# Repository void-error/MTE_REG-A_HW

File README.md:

# MTE_REG-A_HW
Voltage regulators for the analog section

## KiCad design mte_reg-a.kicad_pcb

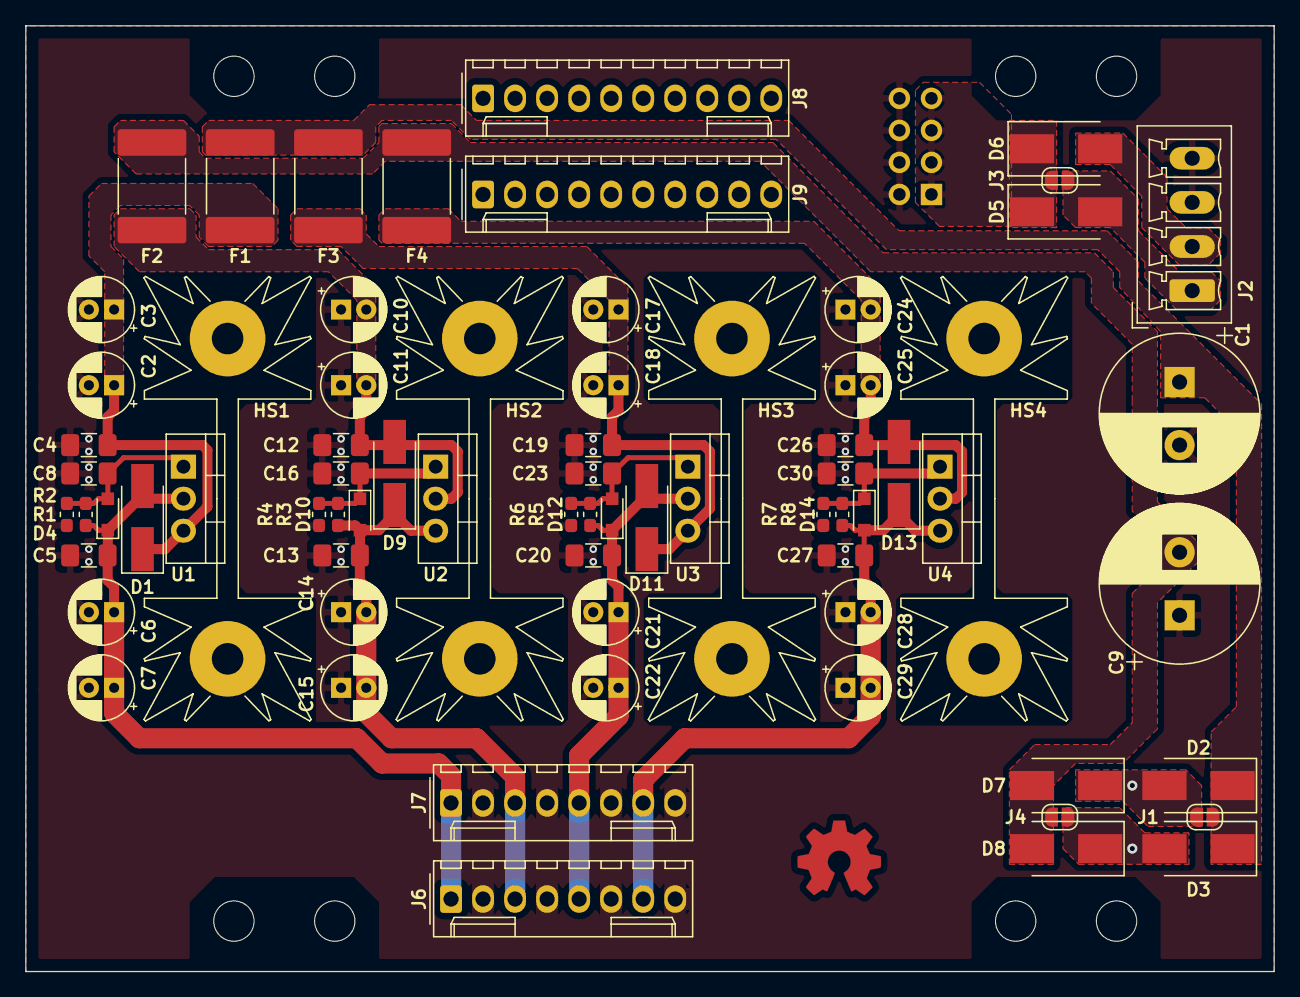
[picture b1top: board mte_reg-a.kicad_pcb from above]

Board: 2 copper layers, 99.0 x 75.0 mm, 82 parts (1 on the bottom side), 28 nets.

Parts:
C1, C9: 1000u; CP_Radial_D12.5mm_P5.00mm
C2, C3, C6, C7, C10, C11, C14, C15, C17, C18, C21, C22, C24, C25, C28, C29: 33u; CP_Radial_D5.0mm_P2.00mm
C4, C5, C12, C13, C19, C20, C26, C27: 330n; C_1206_3216Metric_Pad1.42x1.75mm_HandSolder
C8, C16, C23, C30: 2u2; C_1206_3216Metric_Pad1.42x1.75mm_HandSolder
D1, D9, D11, D13: S1A; D_SMA_Handsoldering
D2, D3, D5, D6, D7, D8: SK55; D_SMB_Handsoldering
D4, D10, D12, D14: BAS316; D_SOD-323_HandSoldering
F1, F2, F3, F4: SL075-33; Fuse_2920_7451Metric_Pad2.10x5.45mm_HandSolder
HS1, HS2, HS3, HS4: SK104; Heatsink_Fischer_SK104-STC-STIC_35x13mm_2xDrill2.5mm
J1, J3, J4: GS2; SolderJumper-2_P1.3mm_Open_RoundedPad1.0x1.5mm
J2: Conn_01x04; PhoenixContact_MCV_1,5_4-G-3.5_1x04_P3.50mm_Vertical
J5: Conn_02x04_Odd_Even; PinSocket_2x04_P2.54mm_Vertical
J6, J7: MOLEX_KK-254; Molex_KK-254_AE-6410-08A_1x08_P2.54mm_Vertical
J8, J9: Conn_01x10; Molex_KK-254_AE-6410-10A_1x10_P2.54mm_Vertical
LOGO1: OSHW; OSHW-Symbol_6.7x6mm_Copper
MK1, MK2, MK3, MK4, MK5, MK6, MK7, MK8: Mounting_Hole; MountingHole_3.2mm_M3
R1, R3, R5, R7: 180R; R_0603_1608Metric_Pad1.05x0.95mm_HandSolder
R2, R4: 2k; R_0603_1608Metric_Pad1.05x0.95mm_HandSolder
R6, R8: 300R; R_0603_1608Metric_Pad1.05x0.95mm_HandSolder
U1, U3: LM317; TO-220-3_Vertical
U2, U4: LM337; TO-220-3_Vertical

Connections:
+V: C1.1, D2.1, D3.1, F1.2, F3.2, J1.1
-V: C9.2, D7.2, D8.2, F2.2, F4.2, J4.1
/VCC1: C5.1, C6.1, C7.1, D1.2, D4.1, J6.1, J7.1, R1.1, U1.2
/VCC2: C20.1, C21.1, C22.1, D11.2, D12.1, J6.5, J7.5, R5.1, U3.2
/VEE1: C13.1, C14.2, C15.2, D9.1, D10.2, J6.3, J7.3, R3.1, U2.3
/VEE2: C27.1, C28.2, C29.2, D13.1, D14.2, J6.7, J7.7, R7.1, U4.3
AGND: C1.2, C2.2, C3.2, C4.2, C5.2, C6.2, C7.2, C8.2, C9.1, C10.1, C11.1, C12.2, C13.2, C14.1, C15.1, C16.2, C17.2, C18.2, C19.2, C20.2, C21.2, C22.2, C23.2, C24.1, C25.1, C26.2, C27.2, C28.1, C29.1, C30.2, J2.3, J2.4, J5.2, J5.4, J5.6, J5.8, J6.2, J6.4, J6.6, J6.8, J7.2, J7.4, J7.6, J7.8, R2.2, R4.2, R6.2, R8.2
unnamed: C2.1, C3.1, C4.1, D1.1, F1.1, U1.3
unnamed: C8.1, D4.2, R1.2, R2.1, U1.1
unnamed: C10.2, C11.2, C12.1, D9.2, F2.1, U2.2
unnamed: C16.1, D10.1, R3.2, R4.1, U2.1
unnamed: C17.1, C18.1, C19.1, D11.1, F3.1, U3.3
unnamed: C23.1, D12.2, R5.2, R6.1, U3.1
unnamed: C24.2, C25.2, C26.1, D13.2, F4.1, U4.2
unnamed: C30.1, D14.1, R7.2, R8.1, U4.1
unnamed: D2.2, D5.2, D7.1, J1.2, J2.1, J3.1
unnamed: D3.2, D6.2, D8.1, J2.2, J4.2
unnamed: D5.1, D6.1, J3.2, J5.1, J5.3, J5.5, J5.7
unnamed: J8.1, J9.1
unnamed: J8.2, J9.2
unnamed: J8.3, J9.3
unnamed: J8.4, J9.4
unnamed: J8.5, J9.5
unnamed: J8.6, J9.6
unnamed: J8.7, J9.7
unnamed: J8.8, J9.8
unnamed: J8.9, J9.9
unnamed: J8.10, J9.10

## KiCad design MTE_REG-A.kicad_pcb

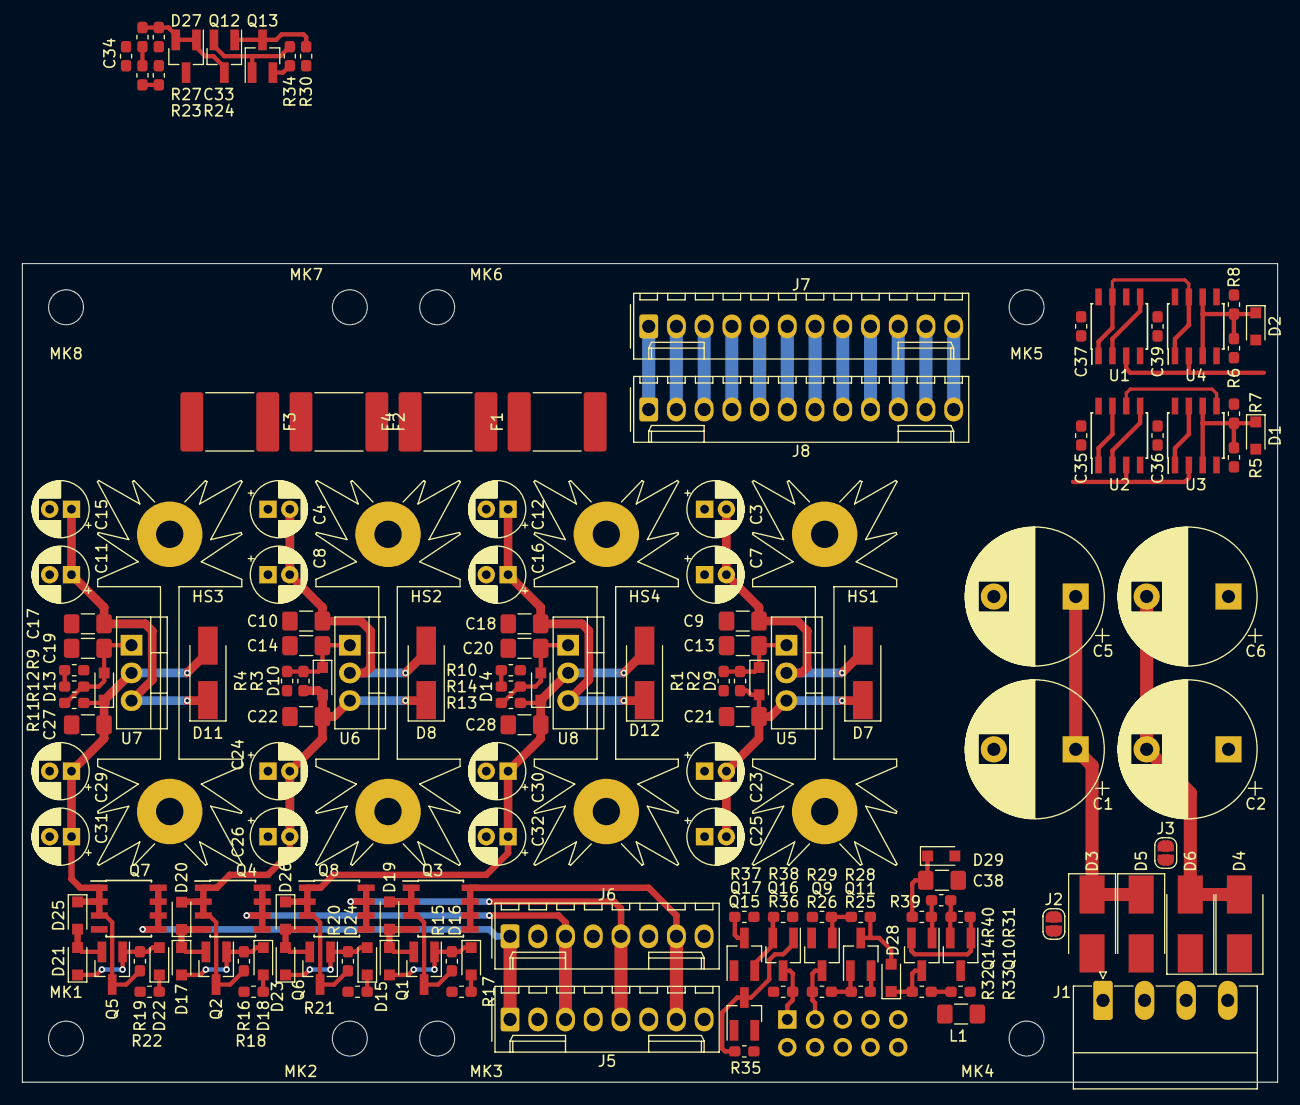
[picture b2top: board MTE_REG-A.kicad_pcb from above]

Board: 2 copper layers, 115.0 x 75.0 mm, 159 parts (1 on the bottom side), 68 nets.

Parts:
C1, C2, C5, C6: 1000u; CP_Radial_D12.5mm_P7.50mm
C3, C4, C7, C8, C11, C12, C15, C16, C23, C24, C25, C26, C29, C30, C31, C32: 33u; CP_Radial_D5.0mm_P2.00mm
C9, C10, C17, C18, C21, C22, C27, C28: 330n; C_1206_3216Metric_Pad1.42x1.75mm_HandSolder
C13, C14, C19, C20, C38: 2u2; C_1206_3216Metric_Pad1.42x1.75mm_HandSolder
C33, C34: 10n; C_0603_1608Metric_Pad1.05x0.95mm_HandSolder
C35, C36, C37, C39: 100n; C_0603_1608Metric_Pad1.05x0.95mm_HandSolder
D1, D2, D9, D10, D13, D14, D15, D16, D17, D18, D21, D22, D23, D24, D28, D29: BAS316; D_SOD-323_HandSoldering
D3, D4, D5, D6: SK55; D_SMB_Handsoldering
D7, D8, D11, D12: S1A; D_SMA_Handsoldering
D19, D20, D25, D26: MM3Z10; D_SOD-323_HandSoldering
D27: TL431DBZ; SOT-23_Handsoldering
F1, F2, F3, F4: SL110-33; Fuse_2920_7451Metric_Pad2.10x5.45mm_HandSolder
HS1, HS2, HS3, HS4: SK104; Heatsink_Fischer_SK104-STC-STIC_35x13mm_2xDrill2.5mm
J1: Conn_01x04; PhoenixContact_MC_1,5_4-G-3.81_1x04_P3.81mm_Horizontal
J2, J3: GS2; SolderJumper-2_P1.3mm_Open_RoundedPad1.0x1.5mm
J4: Conn_02x05_Odd_Even; PinHeader_2x05_P2.54mm_Vertical
J5, J6: MOLEX_KK-254; Molex_KK-254_AE-6410-08A_1x08_P2.54mm_Vertical
J7, J8: MOLEX_KK-254; Molex_KK-254_AE-6410-12A_1x12_P2.54mm_Vertical
L1: Ferrite_Bead; L_1206_3216Metric_Pad1.42x1.75mm_HandSolder
LOGO1: OSHW; OSHW-Symbol_6.7x6mm_Copper
MK1, MK2, MK3, MK4, MK5, MK6, MK7, MK8: Mounting_Hole; MountingHole_3.2mm_M3
Q1, Q2, Q10, Q11, Q12, Q13, Q14, Q17: BC857; SOT-23_Handsoldering
Q3, Q4: IRF7403; SOIC-8_3.9x4.9mm_P1.27mm
Q5, Q6, Q9, Q15, Q16: BC847; SOT-23_Handsoldering
Q7, Q8: IRF7404; SOIC-8_3.9x4.9mm_P1.27mm
R1, R3, R10, R13: 180R; R_0603_1608Metric_Pad1.05x0.95mm_HandSolder
R2: 300R; R_0603_1608Metric_Pad1.05x0.95mm_HandSolder
R4: 2k; R_0603_1608Metric_Pad1.05x0.95mm_HandSolder
R5, R24, R25, R26, R27, R28, R29, R32, R33, R35, R36, R37, R40: 33k; R_0603_1608Metric_Pad1.05x0.95mm_HandSolder
R6, R39: 270k; R_0603_1608Metric_Pad1.05x0.95mm_HandSolder
R7, R31, R38: 7k5; R_0603_1608Metric_Pad1.05x0.95mm_HandSolder
R8: 22k; R_0603_1608Metric_Pad1.05x0.95mm_HandSolder
R9, R11: 150R; R_0603_1608Metric_Pad1.05x0.95mm_HandSolder
R12: 1k5; R_0603_1608Metric_Pad1.05x0.95mm_HandSolder
R14: 120R; R_0603_1608Metric_Pad1.05x0.95mm_HandSolder
R15, R16, R17, R18, R19, R20, R21, R22, R23: 3k6; R_0603_1608Metric_Pad1.05x0.95mm_HandSolder
R30: 10k; R_0603_1608Metric_Pad1.05x0.95mm_HandSolder
R34: 56R; R_0603_1608Metric_Pad1.05x0.95mm_HandSolder
U1, U2, U3, U4: LM393N; SOIC-8_3.9x4.9mm_P1.27mm
U5, U6: LM337; TO-220-3_Vertical
U7, U8: LM317; TO-220-3_Vertical

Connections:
+V: C1.1, C5.1, C35.1, C36.1, C37.1, C39.1, D3.1, D5.1, F3.2, F4.2, J2.1, L1.2, Q10.2, Q11.2, Q13.2, R25.1, R31.1, R34.1, R35.1, R36.2, R39.1, U1.8, U2.8, U3.8, U4.8
-V: C2.2, C6.2, D4.2, D6.2, F1.1, F2.1, J3.1, R37.2
/PG: J4.3, Q9.3, R26.2, U1.1, U1.7, U2.1, U2.7, U3.1, U3.7, U4.1, U4.7
/REF: C33.1, D27.1, D27.2, Q12.3, R7.2, R8.1, R27.1
/REF_HI: C34.1, R23.1, R27.2, U1.3, U2.3, U3.2, U4.2
/REF_LO: R23.2, R24.2, U1.6, U2.6, U3.5, U4.5
/SD: J4.1, Q16.3, R21.1, R22.1, R36.1
/UMON_VCC1: R9.2, R12.2, U1.2, U1.5
/UMON_VCC2: R10.2, R14.2, U2.2, U2.5
/UMON_VEE1: D2.1, R6.1, R8.2, U4.3, U4.6
/UMON_VEE2: D1.1, R5.2, R7.1, U3.3, U3.6
/VCC1: J5.1, J6.1, Q7.5, Q7.6, Q7.7, Q7.8
/VCC2: J5.5, J6.5, Q8.5, Q8.6, Q8.7, Q8.8
/VEE1: J5.3, J6.3, Q4.5, Q4.6, Q4.7, Q4.8
/VEE2: J5.7, J6.7, Q3.5, Q3.6, Q3.7, Q3.8
/~SD~: Q17.3, R17.1, R18.1, R37.1
AGND: C1.2, C2.1, C3.1, C4.1, C5.2, C6.1, C7.1, C8.1, C9.2, C10.2, C11.2, C12.2, C13.2, C14.2, C15.2, C16.2, C17.2, C18.2, C19.2, C20.2, C21.2, C22.2, C23.1, C24.1, C25.1, C26.1, C27.2, C28.2, C29.2, C30.2, C31.2, C32.2, C33.2, C34.2, C35.2, C36.2, C37.2, C38.2, C39.2, D1.2, D2.2, D27.3, D29.2, J1.3, J1.4, J4.2, J4.4, J4.6, J4.8, J4.10, J5.2, J5.4, J5.6, J5.8, J6.2, J6.4, J6.6, J6.8, Q9.2, Q15.2, Q17.1, R2.2, R4.2, R9.1, R10.1, R24.1, R29.2, R30.2, R33.1, R38.2, U1.4, U2.4, U3.4, U4.4
unnamed: C3.2, C7.2, C9.1, D7.2, F1.2, HS1.1, U5.2
unnamed: C4.2, C8.2, C10.1, D8.2, F2.2, HS2.1, U6.2
unnamed: C11.1, C15.1, C17.1, D11.1, F3.1, U7.3
unnamed: C12.1, C16.1, C18.1, D12.1, F4.1, U8.3
unnamed: C13.1, D9.1, R1.2, R2.1, U5.1
unnamed: C14.1, D10.1, R3.2, R4.1, U6.1
unnamed: C19.1, D13.2, R11.2, R12.1, U7.1
unnamed: C20.1, D14.2, R13.2, R14.1, U8.1
unnamed: C21.1, C23.2, C25.2, D7.1, D9.2, D19.2, Q1.3, Q3.1, Q3.2, Q3.3, R1.1, R5.1, R15.1, U5.3
unnamed: C22.1, C24.2, C26.2, D8.1, D10.2, D20.2, Q2.3, Q4.1, Q4.2, Q4.3, R3.1, R6.2, R16.1, U6.3
unnamed: C27.1, C29.1, C31.1, D11.2, D13.1, D25.1, HS3.1, Q5.3, Q7.1, Q7.2, Q7.3, R11.1, R19.1, U7.2
unnamed: C28.1, C30.1, C32.1, D12.2, D14.1, D26.1, HS4.1, Q6.3, Q8.1, Q8.2, Q8.3, R13.1, R20.1, U8.2
unnamed: C38.1, D29.1, R40.2
unnamed: D3.2, D4.1, J1.1, J2.2
unnamed: D5.2, D6.1, J1.2, J3.2
unnamed: D15.1, D19.1, Q1.2, Q3.4
unnamed: D15.2, D16.1, Q1.1, R15.2
unnamed: D16.2, R17.2
unnamed: D17.1, D20.1, Q2.2, Q4.4
unnamed: D17.2, D18.1, Q2.1, R16.2
unnamed: D18.2, R18.2
unnamed: D21.1, D22.2, Q5.1, R19.2
unnamed: D21.2, D25.2, Q5.2, Q7.4
unnamed: D22.1, R22.2
unnamed: D23.1, D24.2, Q6.1, R20.2
unnamed: D23.2, D26.2, Q6.2, Q8.4
unnamed: D24.1, R21.2
unnamed: D28.1, Q14.3, R32.2
unnamed: D28.2, Q11.3, R28.2
unnamed: J4.5, J4.7, J4.9, L1.1
unnamed: J7.1, J8.1
unnamed: J7.2, J8.2
unnamed: J7.3, J8.3
unnamed: J7.4, J8.4
unnamed: J7.5, J8.5
unnamed: J7.6, J8.6
unnamed: J7.7, J8.7
unnamed: J7.8, J8.8
unnamed: J7.9, J8.9
unnamed: J7.10, J8.10
unnamed: J7.11, J8.11
unnamed: J7.12, J8.12
unnamed: Q9.1, R28.1, R29.1
unnamed: Q10.1, Q14.2, R31.2
unnamed: Q10.3, Q11.1, R25.2, R26.1
unnamed: Q12.1, Q13.3, R30.1
unnamed: Q12.2, Q13.1, R34.2
unnamed: Q14.1, R39.2, R40.1
unnamed: Q15.1, R32.1, R33.2
unnamed: Q15.3, Q16.1, R35.2
unnamed: Q16.2, Q17.2, R38.1

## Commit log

2018-02-28 Added KiCad project files, schematic in PDF format, license
2018-02-28 Changed LOGO1 value
2018-11-25 Renamed stuff, updated custom libraries
2018-11-25 Updated PDF
2019-12-27 Revised schematic, initial PCB layout complete
2019-12-27 Fixed library references
2019-12-27 Adjusted board width
2020-01-09 Fixed library name, removed unused file

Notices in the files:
mte_reg-a.kicad_pcb:
License: TAPR Open Hardware License - https://www.tapr.org/ohl
